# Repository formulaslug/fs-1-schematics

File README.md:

# Summary
This repository contains Kicad schematics and PCB layouts for all electrical systems on FS-1.

# Getting Started
* Install the **Github Flavored Markdown** Chrome extension here: https://chrome.google.com/webstore/detail/github-flavored-markdown/faelggnmhofdamhdegcdhhemfokkfngk?hl=en
* Follow the [Getting Started with Electrical](https://drive.google.com/open?id=1L1viwzrDSNJtUvsPxIs5Tox_gefWKw_3um9R9QZQ264) document in the FS Wiki on the Team Drive.

# Schematics
* [AccumulatorBoardHV](AccumulatorBoardHV/README.md): Board containing Vicor and temperature system DCDC converters, 60V threshold circuit for accumulator indicators, and charging relays
* [AccumulatorBoardLV](AccumulatorBoardLV/README.md): Board containing BMS/temp/IMD fault latching and temperature system.
* [AccumulatorElectronics](AccumulatorElectronics/README.md): Wiring schematic of the Accumulator electronics area
* [BatteryTempMonitor](BatteryTempMonitor/README.md): Single-board temperature system implementation, now split between other Accumulator boards
* [Brake Light](Brake Light/README.md): Brake Light PCB
* [Dash](Dash/README.md): Wiring schematic for dash
* [DashSwitchbox](DashSwitchbox/README.md): Switchbox PCB for Dash
* [PEBoardHV](PEBoardHV/README.md): Board containing discharge circuitry and CAN isolation for Sevcons, as well as 60V threshold circuitry for TSAL
* [PEBoardLV](PEBoardLV/README.md): Board containing ECU, BSPD, and h-bridge to drive TSAL, RTDS, and brake light
* [PEBox](PEBox/README.md): Wiring schematic for power electronics
* [Temperature Shield](Temperature Shield/README.md): Battery Cell Shield, facilitates connections between batteries and the temperature/BMS system
* [TSAL](TSAL/README.md): Board containing TSAL oscillator and LEDs, as well as RTDS piezo

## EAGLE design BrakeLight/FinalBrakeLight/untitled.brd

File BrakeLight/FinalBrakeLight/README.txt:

These files were created in Eagle. 
Silk Layer is not complete and connector may change. 
Dimensions are in PNG file.

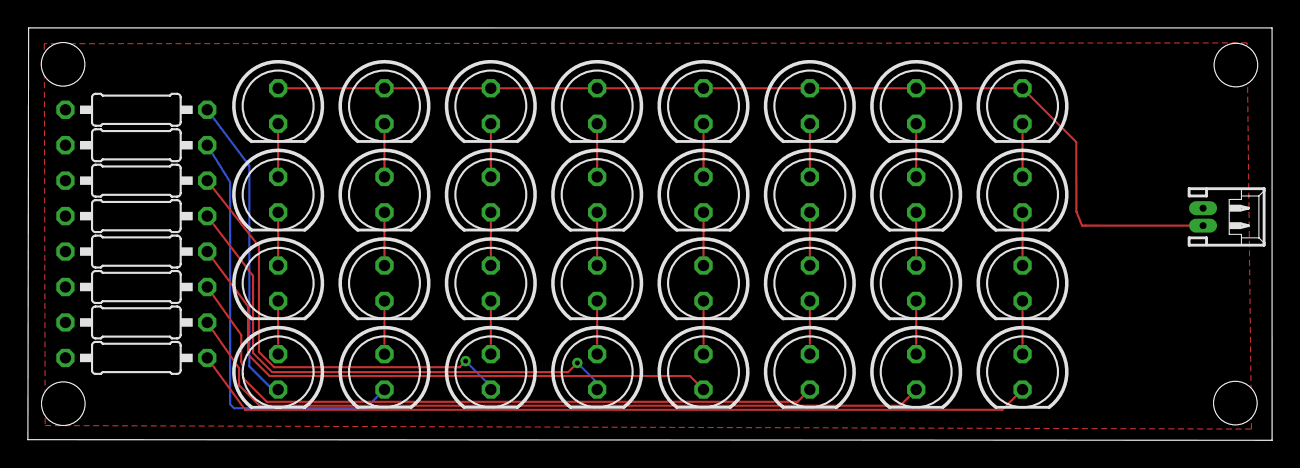
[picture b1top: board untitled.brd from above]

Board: 2 copper layers, 89.2 x 29.5 mm, 41 parts (0 on the bottom side), 34 nets.

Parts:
LED1, LED2, LED3, LED4, LED5, LED6, LED7, LED8, LED9, LED10, LED11, LED12, LED13, LED14, LED15, LED16, LED17, LED18, LED19, LED20, LED21, LED22, LED23, LED24, LED25, LED26, LED27, LED28, LED29, LED30, LED31, LED32: LED5MM
R1, R2, R3, R4, R5, R6, R7, R8: 180; 0207/10
X1: 53048-02

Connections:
GND: R1.1, R2.1, R3.1, R4.1, R5.1, R6.1, R7.1, R8.1, X1.2
unnamed: LED19.A, LED20.K
unnamed: LED18.A, LED19.K
unnamed: LED17.A, LED18.K
unnamed: LED31.A, LED32.K
unnamed: LED17.K, R5.2
unnamed: LED30.A, LED31.K
unnamed: LED29.A, LED30.K
unnamed: LED27.A, LED28.K
unnamed: LED26.A, LED27.K
unnamed: LED25.A, LED26.K
unnamed: LED29.K, R8.2
unnamed: LED25.K, R7.2
unnamed: LED23.A, LED24.K
unnamed: LED22.A, LED23.K
unnamed: LED21.A, LED22.K
unnamed: LED21.K, R6.2
unnamed: LED15.A, LED16.K
unnamed: LED14.A, LED15.K
unnamed: LED13.A, LED14.K
unnamed: LED13.K, R4.2
unnamed: LED11.A, LED12.K
unnamed: LED10.A, LED11.K
unnamed: LED9.A, LED10.K
unnamed: LED9.K, R3.2
unnamed: LED7.A, LED8.K
unnamed: LED6.A, LED7.K
unnamed: LED5.A, LED6.K
unnamed: LED5.K, R2.2
unnamed: LED3.A, LED4.K
unnamed: LED2.A, LED3.K
unnamed: LED1.A, LED2.K
unnamed: LED1.K, R1.2
VCC: LED4.A, LED8.A, LED12.A, LED16.A, LED20.A, LED24.A, LED28.A, LED32.A, X1.1

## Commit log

2017-01-25 Begin working on power electronics box and copied over FS-0 library
2017-01-27 Added brake light to FS library
2017-02-01 Both PEBoard and PEBox, now are separate schematics
2017-02-01 Finish up PEboard
2017-02-02 Add connectors for interlocks for three phase connectors to PEBoard
2017-02-05 Add TSAL schematic from fs-0
2017-02-05 Add Deutsch EEC box pcb package as well as arduino library for STM package
2017-02-05 Start ECU
2017-02-06 Add DIP package MCP2515 to FS library
2017-02-06 Add voltage reg and MCP2515 SPI CAN to FS lib
2017-02-06 Continue working on ECU schematic
2017-02-08 Begin accumulator board, latching for IMD/BMS
2017-02-12 Add 60V switching
2017-02-13 Added Temp Shield
2017-02-15 something idk temp boards or whatever
2017-02-19 Continue BSPD on accumulator board
2017-02-19 Fix library issues
2017-02-21 Add comparators for BSPD
2017-02-21 Begin connectors for Accumulator board
2017-02-22 Add vicor regulator module
2017-02-22 Add actual Vicor file
2017-02-24 Cosmetic work on accumulator board
2017-02-26 Add power symbols and new latching design to Accumulator board
2017-02-28 Add latching circuits for all components
2017-03-01 Add timing delay for fault startup
2017-03-01 Set up 555 timer for new BSPD
2017-03-02 Make BSPD fault-state low and implement startup latching delay
2017-03-02 Add AccumulatorElectronics schematic
2017-03-02 Add BSPD test jumper
2017-03-03 Edit packages for items
2017-03-03 Make BSPD fully fault low
2017-03-04 Add temp board shell and made BSPD fully fault low
2017-03-04 Add more energy meter connectors to PE board, EM may move to accumulator
2017-03-05 Organize ECU sheet better
2017-03-05 Downsize ECU to A4
2017-03-05 Add LV fuse after Vicor
2017-03-06 Add dash
2017-03-06 Add dash button pins to ECU
2017-03-06 Update PE board - move e-meter out and update interlocks
2017-03-12 Added initial schematic for battery temp monitor system
2017-03-12 Move TSAL to PE box
2017-03-13 Add fusing to TSAL line
2017-03-14 Changed MCP3008 to the FS_FINAL version
2017-03-14 Fixed battery temp monitor wiring
2017-03-14 Fix libraries in temp monitor project
2017-03-22 Add dash to library
2017-03-22 Added voltage regulator, diode, and I/O connectors to CTMS
2017-03-29 Revisions for ESF
2017-06-04 Schematic changes from real life testing
2017-06-04 Modify system for changes discovered about relays
2017-06-25 Update based on finalized wire harness
2017-06-25 Added TE Ampseal footprints
2017-06-25 Add board for Dash Switchbox
2017-06-30 Added footprint for latching relay
2017-07-03 Adding bypass caps and adding LV relays to HV board
2017-08-03 Temp Board
2017-08-04 Brake Light
2017-08-27 Begin work on moving ECU to PE box
2017-08-27 Set unix line endings on files
2017-08-27 Enforce line endings with gitattributes file
2017-08-27 Improved 60v threshold circuit for accumulator
2017-08-28 Clean up LV accumulator schematic
    Need to solidify connections between accumulator LV board and temp board
2017-08-30 Add connections to temp board for isolation and fault feedback
2017-09-01 Brake Light Schematic and PCB
2017-09-08 Progress on PE LV and HV boards
    Upgraded to Kicad 4.0.7
2017-09-09 Complete dash switchbox schematic
2017-09-09 Hopefully finalize PCB schematics
2017-09-15 Added hierarchy and templates for markdown docs
2017-09-17 Updated components in temp schematic; re-aligned wiring
2017-09-17 Updated non-modular temp and added SPI isolator chip
2017-09-19 Changed vcc1 (digital supply) of CAN transceiver to 3.3V
2017-09-19 Added bypass cap for HV side of SPI isolator
2017-09-19 Added bypass caps for all SPI ADC chip vref and digital supplies
2017-09-19 Add top-level documentation
2017-09-29 Removed brackets from top level system descriptions
2017-09-30 Cleaned up tracks
2017-10-01 centered LEDs
2017-10-13 Add 3.3v rail to PE HV
2017-10-21 Add wiring for motor sensors
2017-10-21 Fix the connectors between HV and LV boards
2017-12-24 Swapped out vreg for temp system, TS/GLV naming convention, added BMS pull up resistor
2017-12-24 Update to use new latching relays, remove BMS pull up resistor because the relay is the pull up resistor
2018-01-10 Reconfigure dash schematic to take advantage of spare pin
2018-01-13 Add second piezo to TSAL
2018-01-14 Final revision of brake light. Done in Eagle. Info in README
2018-01-15 Completed TSAL schematic and PCB, done in Eagle. NOTE: Ready-to-drive sound NOT implemented yet.
2018-01-16 Added charger control pins and organized optos
2018-01-23 Set footprints for Accumulator HV board, creating necessary ones
2018-01-23 Set footprints for Accumulator LV board, creating necessary ones
2018-02-05 Begin PE/dash footprints, continue with accumulator footprints
2018-02-07 Begin layout of AccumulatorHV board
2018-02-09 AccumulatorLV pcb initial layout
2018-02-10 Dash Switchbox PCB layout
2018-02-12 Work for preparation for autorouting
2018-02-12 Autoroute AccumulatorHV PCB
2018-02-12 Work on LV pcb, having trouble finishing routing
2018-02-12 Revise Accumulator HV and LV, route Dash Switchbox, begin PE HV
2018-02-14 Progress on PE HV PCB layout
2018-02-15 Tweak AccumulatorHV PCB
2018-02-15 Layout and route PE HV board
2018-02-18 Reverse direction of PE HV pcb
2018-02-18 Update footprint cosmetics
2018-02-23 Moved ECU status LEDs to be on the same port
2018-02-23 Completed dual CAN ECU
2018-02-23 WIP: Added all parts for dual CAN ECU and wired some components
2018-02-23 Moved GLV CAN TX/RX to pins available on discovery board
2018-02-25 Lay out rev1 PE LV PCB
2018-02-26 Route rev1 PE LV PCB
2018-02-27 Tweak PE HV board
2018-02-27 Reverse direction of PE LV board
2018-02-27 Update silkscreen component label positioning
2018-02-28 Fixed steering (A-IN), IMD (D-IN), and BSPD (D-OUT) pins
2018-02-28 PE LV Board will be ready to go once routed
    Had to make a couple changes to net size to pass Bay Area Circuit's DFM
2018-02-28 Route V1.0 ECU PCB, should be ready to send for manufacturing
2018-03-01 Add mounting holes to Accumulator HV PCB
2018-03-01 Re-layout Accumulator LV PCB, adding mounting holes
2018-03-01 V2 of PE LV PCB
2018-03-02 Route PE LV PCB with ground plane and vcc plane
2018-03-02 Route PE LV with 4 layers, using center layers as power planes
2018-03-03 Fix grid on the board layout
2018-03-03 Add ground planes to PE HV PCB and add an additional mounting hole
2018-03-03 Fix via size for manufacturing
2018-03-03 Updated TSAL with RTDS. Only needs mounting holes.
2018-03-04 Organized folder paths. Re-did brake light in KiCad. KiCad knowledge overrided eagle knowledge..
2018-03-04 Add more ground/vcc plane bridges to PE LV pcb
2018-03-04 Fix drill sizes for manufacturing on PE HV board
2018-03-04 Add larger fuse to AccumulatorHV board
2018-03-04 Clean out some files from repo
2018-03-05 Add planes to Accumulator LV board
2018-03-05 Create joined PCBs for manufacturing on the same board
    Accumulator one is having problems with the exported files on DFM for some reason
2018-03-06 Finalize the 4 layer PCB
2018-03-06 Select 4 layer version of PE LV board
2018-03-07 Add Charger switchbox
2018-03-07 Tweak routing on boards, add mounting holes to dash switchbox
2018-03-09 Tweak silkscreen labels on boards for final run
2018-03-09 Need to correct Bay Area DFM warnings on TSAL. Brake Light passed and ready to be sent.
2018-03-10 Revise boards based on design review
2018-03-10 Change TSMP resistors
2018-03-11 Tweaks to output schematics for ESF
2018-03-11 Updated TSAL. passed DFM
2018-03-12 Un-fuse TSMPs
2018-03-12 resdesigned tsal. It is circular, much like fs0 tsal.
2018-03-14 Add connections to connectors on PE and Acc LV boards
2018-03-16 redo AccumulatorBoardLV for new accumulator packaging scheme
2018-03-16 Clean up old files from repository
2018-03-19 Reverse connector directions on PE LV board
2018-03-21 update some footprint throughole sizes
2018-03-22 update Arduino (used for STMF3) footprint as well
2018-03-23 edit PCBs based on actual parts that have arrived
2018-03-27 add fuse to CAN+ line on PE HV board
2018-03-27 prepare to re-send PE LV board
2018-03-27 Move LEDs on PE LV board
2018-03-27 fix AccumulatorLV board based on real life testing
2018-03-28 shrink AccumulatorHV PCB
2018-03-29 update for sending out second round of PE LV pcb
2018-03-29 Tweak 60v circuits based on testing results
2018-03-29 push schematic updates for 60V on PE HV
2018-03-29 add circular TSAL with surface mount LEDs
2018-04-03 Add TVS diode and choke to PE HV board
2018-04-08 Update DE relay footprint
2018-04-08 tweak boards slightly
2018-04-11 fix 3.3V reg on ECU footprint
2018-04-21 add diodes to relay coils among other things
2018-04-23 add mounting holes and surface mount resistors to TSAL
2018-04-24 Update 60V circuit some more, on both boards
2018-04-26 move connectors to assist in battery packaging
2018-04-27 temp shield FUCKINGSENDIT
2018-04-28 hopefully finalize PCBs for send to manufacturing
2018-04-29 Edit some component labels and other items for PCB send out
2018-04-29 Add remaining capacitor values to schematics
2018-04-29 add TS/GLV labels to Charger Switchbox pcb
2018-05-01 Fixed temp shields
    Added serial connection between shields bc im dumb and forgot
2018-05-04 update BSPD resistor values
2018-06-04 Final PCB revisions
2019-01-21 Started LTC6811 BMS
2019-01-26 New TSAL beginnings
2019-01-29 TSAL Schematic done
2019-02-11 Updated BMS Schematics
2019-02-13 BMS update
2019-02-13 library stupidity
2019-02-26 Updated BMS
2019-02-27 Begin work on BMS schematic
2019-02-27 Finish layout of TSAL 2019 (ugly edition)
2019-02-27 BMS again
2019-03-05 BMS board v0.1
2019-03-07 Fix TSAL layout to be less garbage
2019-03-10 Add initial BMS master project
2019-03-12 yikes
2019-03-12 Add MSOP-16 Breakout Board
2019-03-31 Update BMS bias resistors and enable pin
2019-04-03 Began BMS slave board
2019-04-03 fixed shit
2019-04-04 BMS update pre-autorouter
2019-04-04 BMS pcb routed
2019-04-07 updated the things
2019-04-08 final lv board routed
2019-04-08 Add termination resistor to isoSPI on Accumulator LV
2019-04-16 Unfucked PELV symbols
2019-04-16 Unfucked Dash
2019-05-29 Torque Vectoring PCB v0.2
2019-05-29 New Molex NanoFit 1x4 footprint that passes DRC ._.
2019-05-30 remapped symbols for PEHV
2020-03-08 CAN Isolator folder
2020-03-08 Moar of previous
2022-12-23 Some changes to hopefully make some projects openable in Kicad 5 and 6
2023-11-04 Make AccLV work in Kicad 4 again
2023-11-04 Convert AccLV to Kicad 7
2023-11-04 Fix AccHV
2023-11-05 Fix up most of the remaining projects
2023-11-05 Fix charger switchbox
